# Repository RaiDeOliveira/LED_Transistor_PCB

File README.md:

# LED_Transistor_PCB

Esse repositório armazena um projeto simples de PCB (Printed Circuit Board, ou Placa de Circuito Impresso em português) de um circuito para acender e apagar um LED a partir de um transistor e um Raspberry Pi Pico.

Essa PCB foi projetada através do software Kicad, que não tem suporte oficial para o Raspberry Pi Pico. Portanto, para abrir e visualizar os arquivos do projeto adequadamente, você deve seguir as instruções [neste outro respositório](https://github.com/ncarandini/KiCad-RP-Pico).

## Estrutura de pastas

```bash
├── img
├── pcb_interruptor
│   ├── pcb_interruptor.kicad_pcb
│   ├── pcb_interruptor.kicad_pro
│   └── pcb_interruptor.kicad_sch
└── README.md
```

- **img** -> Pasta com imagens ilustrativas relacionadas ao projeto
- **pcb_interruptor.kicad_pcb** -> Arquivo de design finalizado da PCB
- **pcb_interruptor.kicad_pro** -> Arquivo principal do projeto da PCB
- **pcb_interruptor.kicad_sch** -> Arquivo de desenho esquemático da PCB
- **README.md** -> Arquivo com informações detalhadas sobre o projeto

## Componentes utilizados

- 1x Raspberry Pi Pico
- 1x Transistor
- 1x Resistor de 1kΩ
- 1x Resistor de 220Ω
- 1x LED simples

## Funcionamento

Com todos os devidos componentes encaixados e ligados conforme o desenho esquemático e com o Raspberry Pi Pico conectado a uma fonte de alimentação (ex.: USB), o LED deverá acender toda vez que o transistor receber energia do pino 27 (GPIO 21). Esse comportamento pode ser programado através de código no Raspberry PI pico.

## Imagens do projeto

### Desenho esquemático

### Design de PCB

### Visualização 3D

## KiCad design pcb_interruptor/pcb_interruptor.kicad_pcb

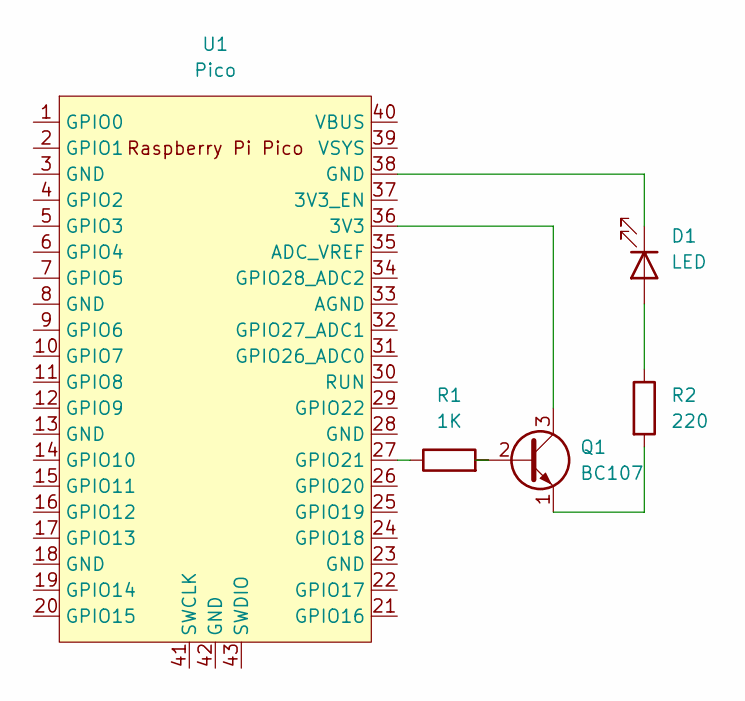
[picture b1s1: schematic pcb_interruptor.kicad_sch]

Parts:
D1: LED; LED_D5.0mm_Horizontal_O6.35mm_Z15.0mm
Q1: BC107; TO-92L
R1: 1K; R_LDR_5.2x5.2mm_P3.5mm_Horizontal
R2: 220; R_LDR_5.2x5.2mm_P3.5mm_Horizontal
U1: Pico; RPi_Pico_SMD_TH

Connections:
unnamed: D1.2 (A), R2.1
unnamed: D1.1 (K), U1.38 (GND)
unnamed: Q1.2 (B), R1.2
unnamed: Q1.3 (C), U1.36 (3V3)
unnamed: Q1.1 (E), R2.2
unnamed: R1.1, U1.27 (GPIO21)

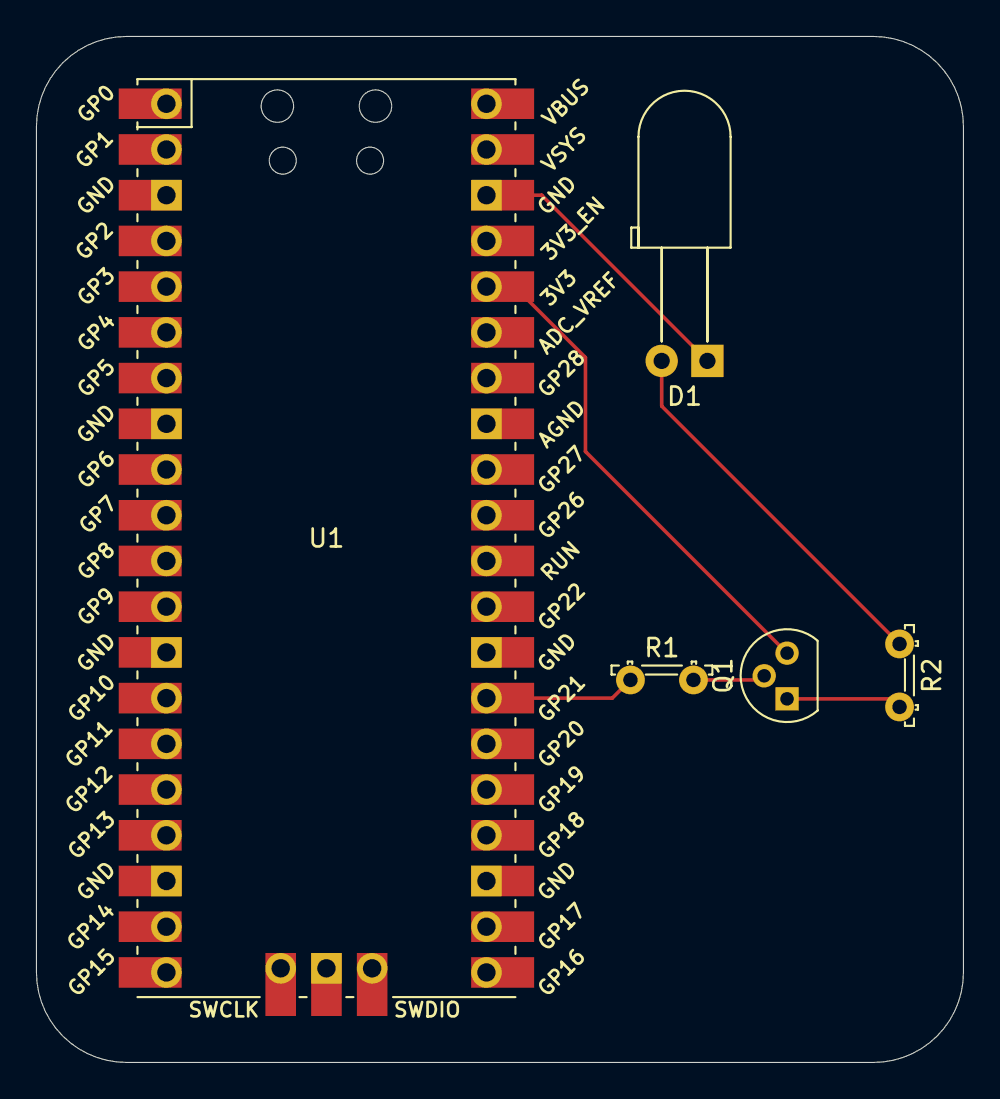
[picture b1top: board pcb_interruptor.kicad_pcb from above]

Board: 2 copper layers, 51.5 x 57.0 mm, 5 parts (0 on the bottom side), 6 nets.

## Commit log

2024-03-31 add: main pcb project files
2024-03-31 docs: add README.md info
2024-03-31 docs: add imgs
2024-03-31 docs: fix list formatting
2024-03-31 docs: fix 3d img & kicad info
